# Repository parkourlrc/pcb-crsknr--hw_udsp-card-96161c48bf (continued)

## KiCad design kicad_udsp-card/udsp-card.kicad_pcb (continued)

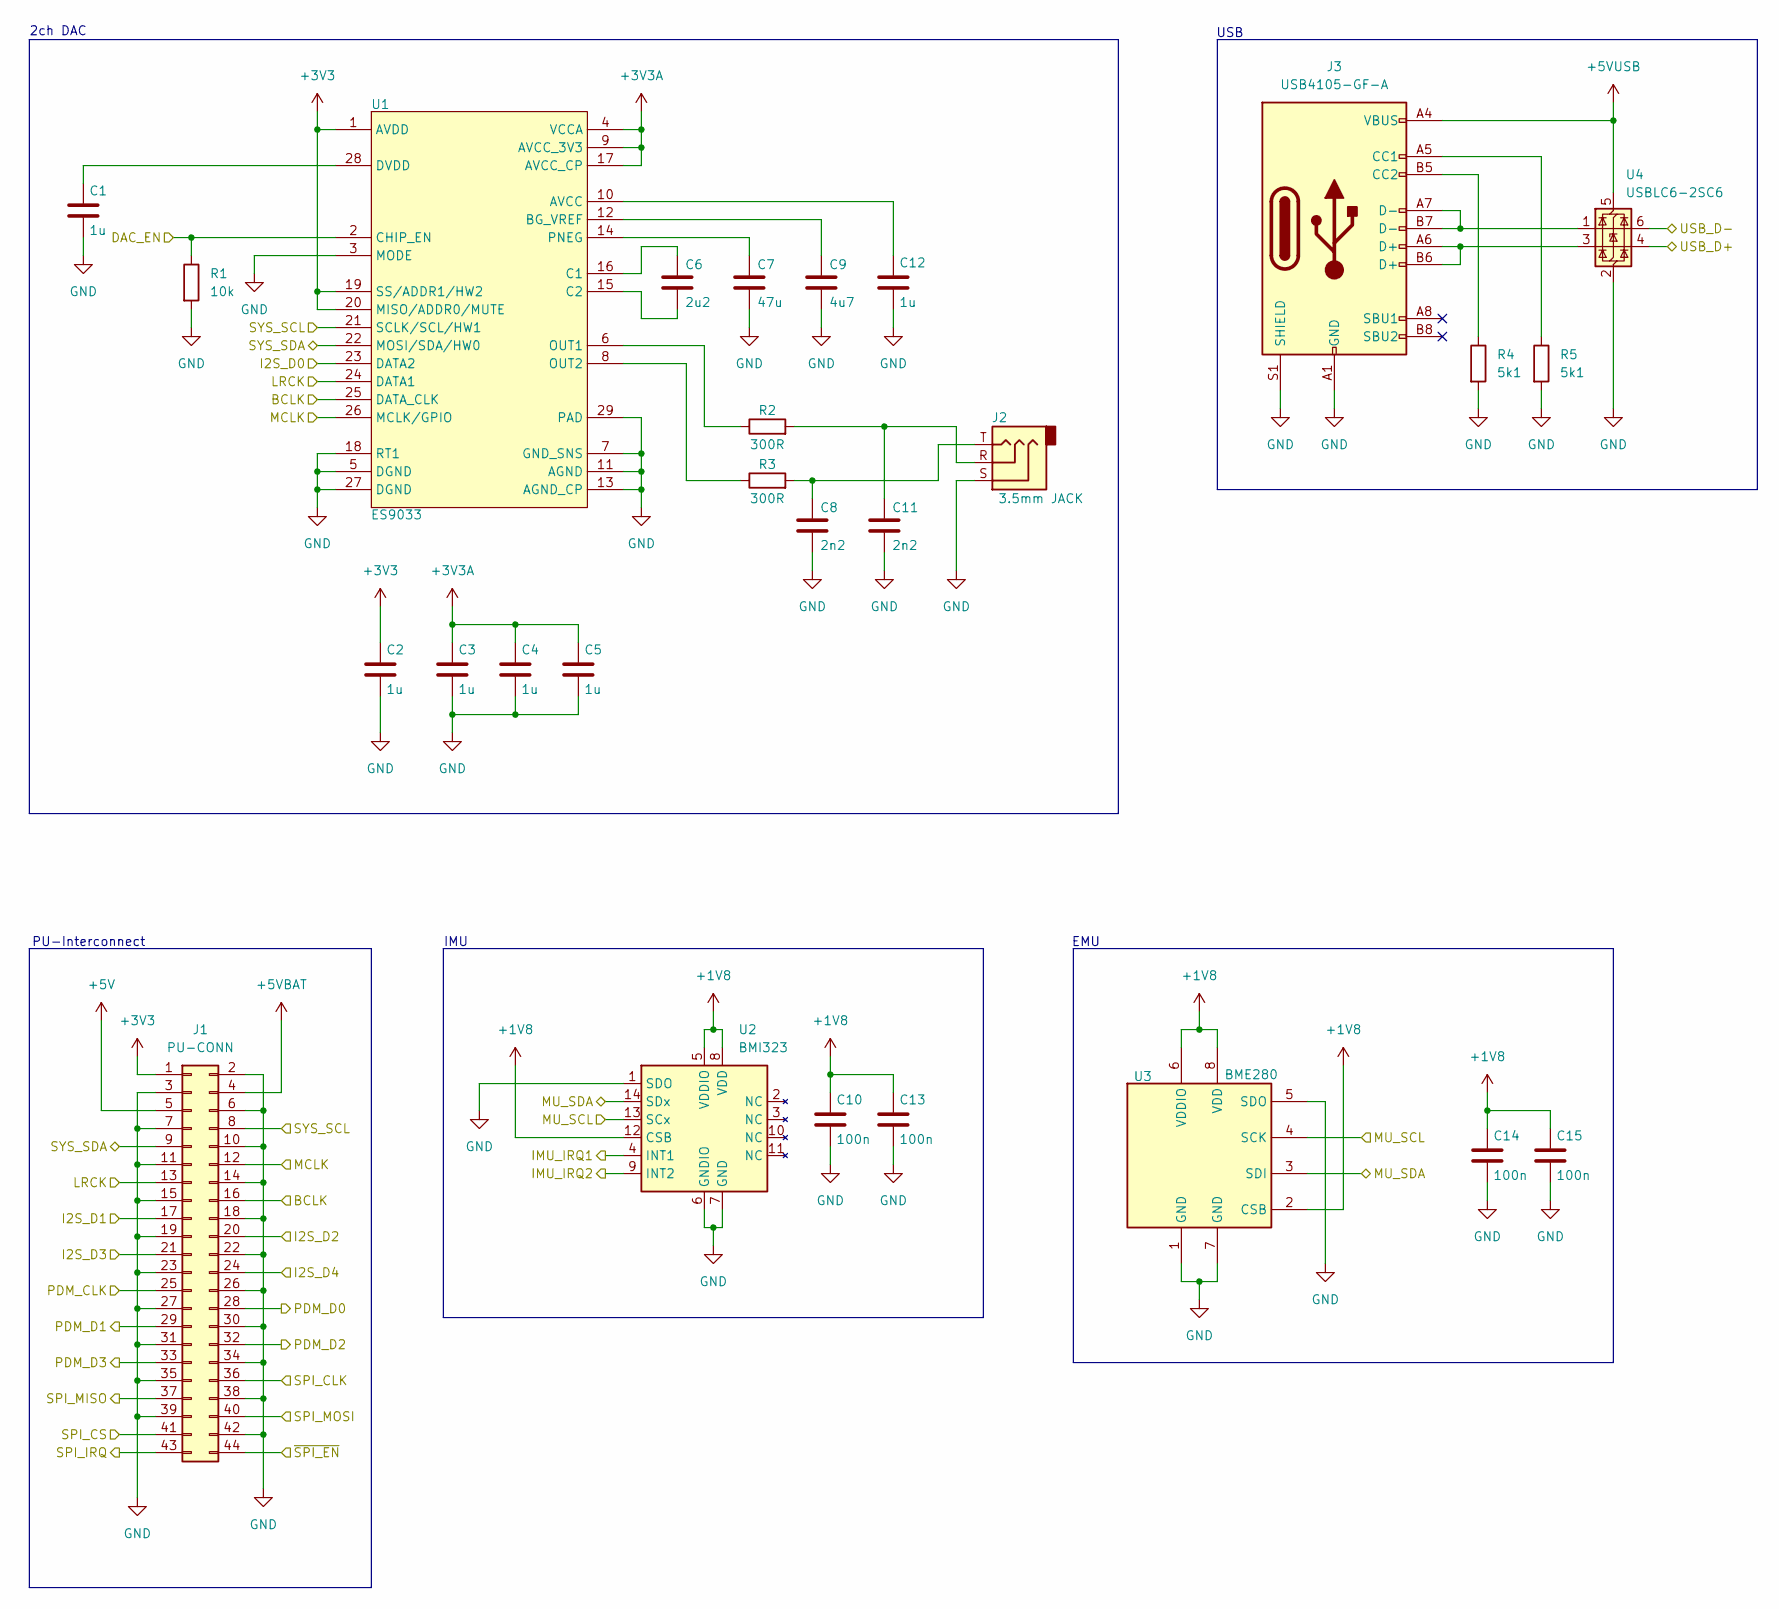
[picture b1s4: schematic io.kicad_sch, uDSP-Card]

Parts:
C1, C2, C3, C4, C5, C12: 1u; C_0402_1005Metric; Part Number CC0402KRX5R7BB105
C6: 2u2; C_0603_1608Metric; Part Number CC0603KRX5R9BB225
C7: 47u; C_0805_2012Metric; Part Number CC0805MKX5R6BB476
C8, C11: 2n2; C_0402_1005Metric; Part Number GRM1555C1H222GA01D
C9: 4u7; C_0603_1608Metric; Part Number CC0603KRX5R7BB475
C10, C13, C14, C15: 100n; C_0402_1005Metric; Part Number CC0402KRX5R9BB104
J1: PU-CONN; SAMTEC_FLE-122-01-G-DV; Part Number FLE-122-01-G-DV
J2: 3.5mm JACK; Jack_3.5mm_CUI_SJ-3523-SMT_Horizontal; Part Number SJ-3523-SMT-TR
J3: USB4105-GF-A; USB_C_Receptacle_GCT_USB4105-xx-A_16P_TopMnt_Horizontal; Part Number USB4105-GF-A
R1: 10k; R_0402_1005Metric; Part Number RC0402FR-0710KL
R2, R3: 300R; R_0402_1005Metric; Part Number RT0402FRE07300RL
R4, R5: 5k1; R_0402_1005Metric; Part Number RC0402FR-075K1L
U1: ES9033; QFN-28-1EP_5x5mm_P0.5mm_EP3.1x3.1mm; Part Number ES9033Q
U2: BMI323; Bosch_LGA-14_3x2.5mm_P0.5mm; Part Number BMI323
U3: BME280; Bosch_LGA-8_2.5x2.5mm_P0.65mm_ClockwisePinNumbering; Part Number BME280
U4: USBLC6-2SC6; SOT-23-6; Part Number USBLC6-2SC6

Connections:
+1V8: C10.1, C13.1, C14.1, C15.1, U2.5 (VDDIO), U2.8 (VDD), U2.12 (CSB), U3.2 (CSB), U3.6 (VDDIO), U3.8 (VDD); also elsewhere on the board
+3V3: C2.1, J1.1, U1.1 (AVDD), U1.19 (SS/ADDR1/HW2), U1.20 (MISO/ADDR0/MUTE); also elsewhere on the board
+3V3A: C3.1, C4.1, C5.1, U1.4 (VCCA), U1.9 (AVCC_3V3), U1.17 (AVCC_CP); also elsewhere on the board
+5V: J1.5; also elsewhere on the board
+5VBAT: J1.4; also elsewhere on the board
+5VUSB: J3.A4 (VBUS), J3.A9 (VBUS), J3.B4 (VBUS), J3.B9 (VBUS), U4.5 (VBUS); also elsewhere on the board
/DAC_EN: R1.1, U1.2 (CHIP_EN); also elsewhere on the board
/I2S.BCLK: J1.16, U1.25 (DATA_CLK); also elsewhere on the board
/I2S.D0: U1.23 (DATA2); also elsewhere on the board
/I2S.D1: J1.17; also elsewhere on the board
/I2S.D2: J1.20; also elsewhere on the board
/I2S.D3: J1.21; also elsewhere on the board
/I2S.D4: J1.24; also elsewhere on the board
/I2S.LRCK: J1.13, U1.24 (DATA1); also elsewhere on the board
/I2S.MCLK: J1.12, U1.26 (MCLK/GPIO); also elsewhere on the board
/IMU_IRQ1: U2.4 (INT1); also elsewhere on the board
/IMU_IRQ2: U2.9 (INT2); also elsewhere on the board
/MIC.CLK: J1.25; also elsewhere on the board
/MIC.D0: J1.28; also elsewhere on the board
/MIC.D1: J1.29; also elsewhere on the board
/MIC.D2: J1.32; also elsewhere on the board
/MIC.D3: J1.33; also elsewhere on the board
/MU.SCL: U2.13 (SCx), U3.4 (SCK); also elsewhere on the board
/MU.SDA: U2.14 (SDx), U3.3 (SDI); also elsewhere on the board
/SPI.CLK: J1.36; also elsewhere on the board
/SPI.CS: J1.41; also elsewhere on the board
/SPI.MISO: J1.37; also elsewhere on the board
/SPI.MOSI: J1.40; also elsewhere on the board
/SPI_IRQ: J1.43; also elsewhere on the board
/SYS.SCL: J1.8, U1.21 (SCLK/SCL/HW1); also elsewhere on the board
/SYS.SDA: J1.9, U1.22 (MOSI/SDA/HW0); also elsewhere on the board
/USB.D+: U4.4 (I/O2); also elsewhere on the board
/USB.D-: U4.6 (I/O1); also elsewhere on the board
/~SPI_EN: J1.44; also elsewhere on the board
GND: C1.2, C2.2, C3.2, C4.2, C5.2, C7.2, C8.2, C9.2, C10.2, C11.2, C12.2, C13.2, C14.2, C15.2, J1.2, J1.3, J1.6, J1.7, J1.10, J1.11, J1.14, J1.15, J1.18, J1.19, J1.22, J1.23, J1.26, J1.27, J1.30, J1.31, J1.34, J1.35, J1.38, J1.39, J1.42, J2.S, J3.A1 (GND), J3.A12 (GND), J3.B1 (GND), J3.B12 (GND), J3.S1 (SHIELD), R1.2, R4.2, R5.2, U1.3 (MODE), U1.5 (DGND), U1.7 (GND_SNS), U1.11 (AGND), U1.13 (AGND_CP), U1.18 (RT1), U1.27 (DGND), U1.29 (PAD), U2.1 (SDO), U2.6 (GNDIO), U2.7 (GND), U3.1 (GND), U3.5 (SDO), U3.7 (GND), U4.2 (GND); also elsewhere on the board
unnamed: C8.1, J2.T, R3.2
unnamed: C11.1, J2.R, R2.2
unnamed: J3.A5 (CC1), R5.1
unnamed: J3.B5 (CC2), R4.1
unnamed: J3.A6 (D+), J3.B6 (D+), U4.3 (I/O2)
unnamed: J3.A7 (D-), J3.B7 (D-), U4.1 (I/O1)
unnamed: C12.1, U1.10 (AVCC)
unnamed: C9.1, U1.12 (BG_VREF)
unnamed: C6.1, U1.16 (C1)
unnamed: C6.2, U1.15 (C2)
unnamed: C1.1, U1.28 (DVDD)
unnamed: R2.1, U1.6 (OUT1)
unnamed: R3.1, U1.8 (OUT2)
unnamed: C7.1, U1.14 (PNEG)

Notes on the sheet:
2ch DAC
IMU
USB
EMU
PU-Interconnect

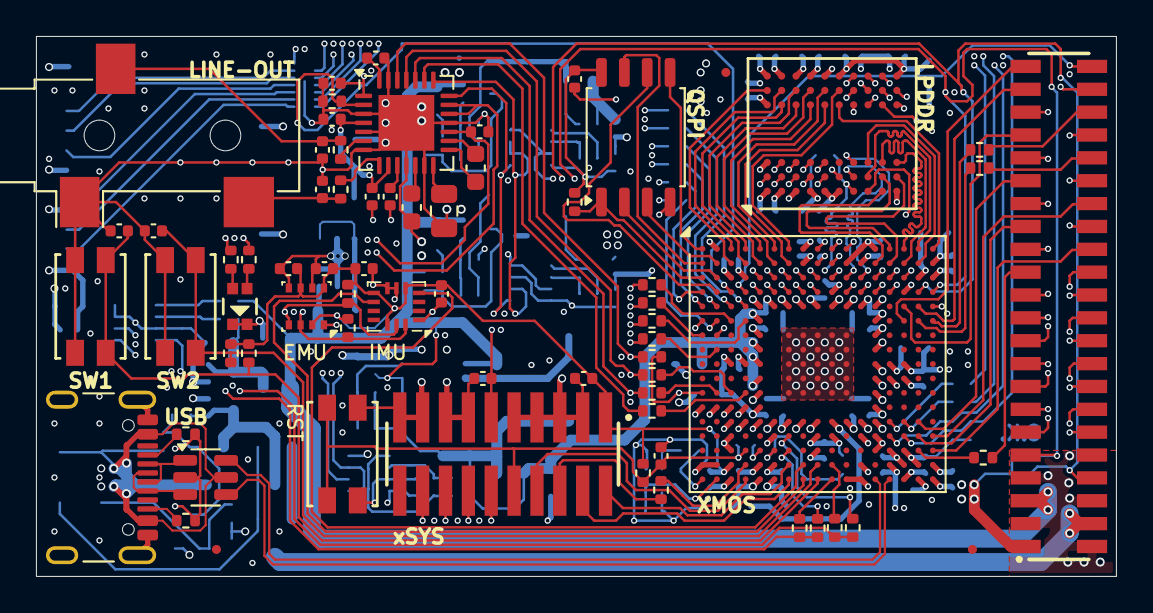
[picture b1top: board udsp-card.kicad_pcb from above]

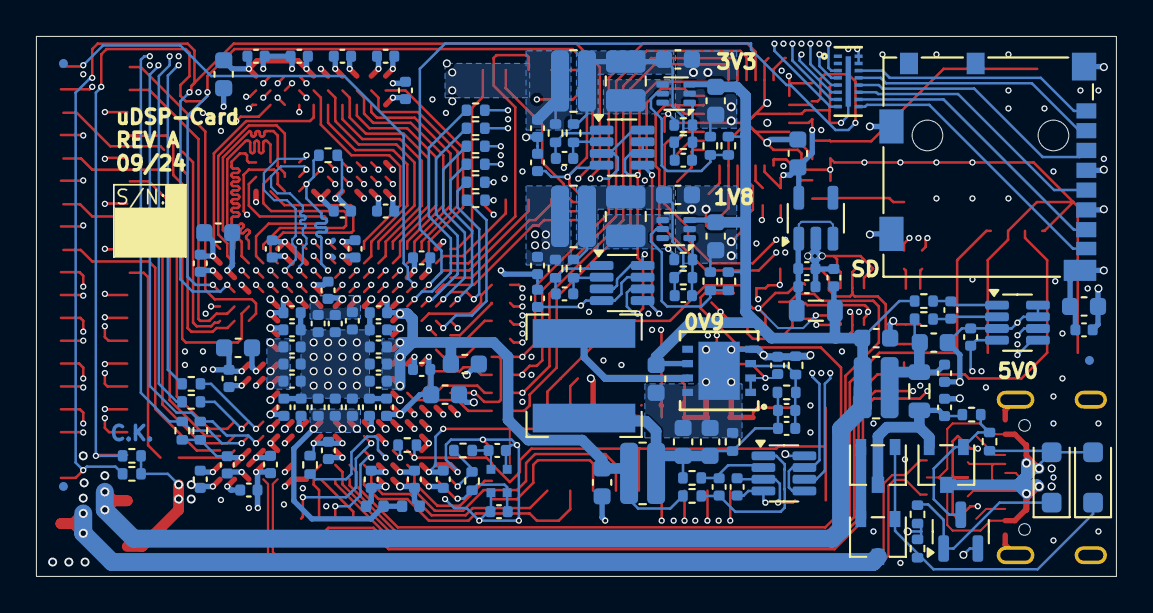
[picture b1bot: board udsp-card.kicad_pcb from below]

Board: 6 copper layers, 60.0 x 30.0 mm, 221 parts (153 on the bottom side), 183 nets.

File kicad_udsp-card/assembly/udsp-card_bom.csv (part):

"Reference","Value","Part Number","Manufacturer","Description","Footprint","Qty","Distributor Link"
"C1,C2,C3,C4,C5,C12,C16,C17,C20,C81,C83,C92,C93","1u","CC0402KRX5R7BB105","Yageo","Multilayer Ceramic Capacitor, 1uF, 16V, 10%, X5R, 0402","Capacitor_SMD:C_0402_1005Metric","13","https://www.lcsc.com/product-detail/Multilayer-Ceramic-Capac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"
"C6","2u2","CC0603KRX5R9BB225 ","Yageo","Multilayer Ceramic Capacitor, 2.2uF, 50V, 10%, X5R, 0603","Capacitor_SMD:C_0603_1608Metric","1","https://www.lcsc.com/product-detail/Multilayer-Ceramic-Capac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"
"C7","47u","CC0805MKX5R6BB476","Yageo","Multilayer Ceramic Capacitor, 47uF, 10V, 20%, X5R, 0805","Capacitor_SMD:C_0805_2012Metric","1","https://www.lcsc.com/product-detail/Multilayer-Ceramic-Capac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"
"C8,C11","2n2","GRM1555C1H222GA01D","Murata Electronics","Multilayer Ceramic Capacitor, 2.2nF, 50V, 2%, NP0, 0402","Capacitor_SMD:C_0402_1005Metric","2","https://www.lcsc.com/product-detail/Multilayer-Ceramic-Capac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"
"C9,C18,C32,C49,C56,C62","4u7","CC0603KRX5R7BB475","Yageo","Multilayer Ceramic Capacitor, 4.7uF, 16V, 10%, X5R, 0603","Capacitor_SMD:C_0603_1608Metric","6","https://www.lcsc.com/product-detail/Multilayer-Ceramic-Capac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"
"C10,C13,C14,C15,C19,C21,C22,C23,C24,C25,C26,C27,C28,C29,C30,C31,C33,C34,C35,C36,C37,C38,C39,C40,C43,C44,C45,C46,C47,C48,C50,C51,C52,C53,C54,C55,C57,C58,C59,C60,C61,C63,C64,C65,C66,C67,C68,C69,C70,C72,C73,C74,C77,C82,C96,C97,C98,C99,C100,C101,C102,C103","100n","CC0402KRX5R9BB104","Yageo","Multilayer Ceramic Capacitor, 100nF, 50V, 10%, X5R, 0402","Capacitor_SMD:C_0402_1005Metric","62","https://www.lcsc.com/product-detail/Multilayer-Ceramic-Capac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"
"C41,C42,C86,C88","18p","CC0402JRNPO9BN180","Yageo","Multilayer Ceramic Capacitor, 18pF, 50V, 5%, NP0, 0402","Capacitor_SMD:C_0402_1005Metric","4","https://www.lcsc.com/product-detail/Multilayer-Ceramic-Capac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"
"C71,C75,C76,C78,C79,C80,C87,C89,C90,C91,C94,C95","10u","CC0603MRX5R7BB106","Yageo","Multilayer Ceramic Capacitor, 10uF, 16V, 20%, X5R, 0603","Capacitor_SMD:C_0603_1608Metric","12","https://www.lcsc.com/product-detail/Multilayer-Ceramic-Capac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"
"C84","470p","CC0402KRX7R7BB471 ","Yageo","Multilayer Ceramic Capacitor, 470pF, 16V, 10%, X7R, 0402","Capacitor_SMD:C_0402_1005Metric","1","https://www.lcsc.com/product-detail/Multilayer-Ceramic-Capac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"
"C85","220p","CC0402KRX7R7BB221","Yageo","Multilayer Ceramic Capacitor, 220pF, 16V, 10%, X7R, 0402","Capacitor_SMD:C_0402_1005Metric","1","https://www.lcsc.com/product-detail/Multilayer-Ceramic-Capac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"
"D1","LTST-C195KGJRKT","LTST-C195KGJRKT","Lite-On","LED dual red/green, 2V, 20mA, 0606","lib_fp_ssh:LTST-C195KGJRKT-NPC_LTO","1","https://www.lcsc.com/product-detail/LED-Indication-Discrete_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"
"D2,D3","1N4148W","1N4148W-E3-08","Vishay Intertech","Diode, 75V, 0.15A, SOD-123F","Diode_SMD:D_SOD-123F","2","https://www.lcsc.com/product-detail/Switching-Diodes_Vishay-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"
"FB1,FB2","600R","BLM15PX601SH1D","Murata","Ferrite Bead, 600R AT 100MHz, 0.9A, 0402","Inductor_SMD:L_0402_1005Metric","2","https://www.mouser.fi/ProductDetail/Murata-Electronics/BLM15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"
"FB3,FB4","180R","BLM21SP181SZ1D","Murata","Ferrite Bead, 180R AT 100MHz, 4.0A, 0805","Inductor_SMD:L_0805_2012Metric","2","https://www.lcsc.com/product-detail/Ferrite-Beads_Murata-Ele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"
"J1","PU-CONN","FLE-122-01-G-DV","Samtec","Socket, 0.050"" Pitch, 2x22, SMD","lib_fp_ssh:SAMTEC_FLE-122-01-G-DV","1","https://www.mouser.fi/ProductDetail/Samtec/FLE-122-01-G-DV-P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"
"J2","3.5mm JACK","SJ-3523-SMT-TR ","CUI Devices","Audio Jack, 3 Poles (Stereo / TRS), SMD","Connector_Audio:Jack_3.5mm_CUI_SJ-3523-SMT_Horizontal","1","https://www.mouser.fi/ProductDetail/CUI-Devices/SJ-3523-SMT-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"
"J3","USB4105-GF-A","USB4105-GF-A","GCT","USB 2.0-only 16P Type-C Receptacle connector","Connector_USB:USB_C_Receptacle_GCT_USB4105-xx-A_16P_TopMnt_Horizontal","1","https://www.mouser.fi/ProductDetail/GCT/USB4105-GF-A?qs=KUoI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"
"J4","xSYS2","FTSH-110-01-F-DV-K","Samtec","Header, 0.050"" Pitch, 2x10, SMD","lib_fp_ssh:SAMTEC_FTSH-110-01-F-DV-TR","1","https://www.lcsc.com/product-detail/Pin-Headers_Samtec-FTSH-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"
"J5","104031-0811","104031-0811","Molex","Micro SD Card Socket with two card detection pins","Connector_Card:microSD_HC_Molex_104031-0811","1","https://www.lcsc.com/product-detail/SD-Card-Memory-Card-Conn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"
"L1,L2","1u5","MAMK2520H1R5M","Taiyo Yuden","Power Inductor, 1.5uH, 2.6A, 65mR DCR, 2.5x2.0x1.2mm, SMD","Inductor_SMD:L_1008_2520Metric","2","https://www.lcsc.com/product-detail/Power-Inductors_Taiyo-Yu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"
"L3","2u2","NR6028T2R2N","Taiyo Yuden","Power Inductor, 2.2uH, 3.7A, 26mR DCR, SMD","Inductor_SMD:L_Bourns-SRN6028","1","https://www.mouser.fi/ProductDetail/TAIYO-YUDEN/NR6028T2R2N?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"
"Q1","2N7002","2N7002A-7","Diodes Incorporated","N-Channel MOSFET, 0.115A, 60V, SOT-23","Package_TO_SOT_SMD:SOT-23","1","https://www.lcsc.com/product-detail/MOSFETs_Diodes-Incorpora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"
"Q2,Q3,Q4","RQ5C060BCTCL","RQ5C060BCTCL","ROHM Semiconductor ","P-Channel MOSFET, 6A, 20V, SOT-346","lib_fp_ssh:SOT346","3","https://www.lcsc.com/product-detail/MOSFETs_ROHM-Semicon-RQ5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"
"R1,R33,R34,R39,R45,R46,R48,R49,R50,R56,R59","10k","RC0402FR-0710KL","Yageo","Thick Film Resistor, 10kOhm, 62.5mW, 1%, 100ppm, 0402","Resistor_SMD:R_0402_1005Metric","11","https://www.lcsc.com/product-detail/Chip-Resistor-Surface-Mo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"
"R2,R3","300R","RT0402FRE07300RL","Yageo","Thin Film Resistor, 300Ohm, 62.5mW, 1%, 50ppm, 0402","Resistor_SMD:R_0402_1005Metric","2","https://www.mouser.fi/ProductDetail/YAGEO/RT0402FRE07300RL?q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"
"R4,R5,R20,R21,R35,R36","5k1","RC0402FR-075K1L","Yageo","Thick Film Resistor, 5.1kOhm, 62.5mW, 1%, 100ppm, 0402","Resistor_SMD:R_0402_1005Metric","6","https://www.lcsc.com/product-detail/Chip-Resistor-Surface-Mo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"
"R6,R7,R8,R9,R10,R11,R12,R13,R14,R15,R16,R17,R18,R19,R27,R40,R41,R42,R43,R44","33R","RC0402FR-0733RL","Yageo","Thick Film Resistor, 33Ohm, 62.5mW, 1%, 100ppm, 0402","Resistor_SMD:R_0402_1005Metric","20","https://www.lcsc.com/product-detail/Chip-Resistor-Surface-Mo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"
"R22","1M","RC0402FR-071ML","Yageo","Thick Film Resistor, 1MOhm, 62.5mW, 1%, 100ppm, 0402","Resistor_SMD:R_0402_1005Metric","1","https://www.lcsc.com/product-detail/Chip-Resistor-Surface-Mo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"
"R30,R31,R32","680R","RC0402FR-07680RL","Yageo","Thick Film Resistor, 680Ohm, 62.5mW, 1%, 100ppm, 0402","Resistor_SMD:R_0402_1005Metric","3","https://www.lcsc.com/product-detail/Chip-Resistor-Surface-Mo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"
"R51","0R01","ERJ-D2DFR010V","Panasonic","Thick Film Resistor, 10mOhm, 1W, 1%, 100ppm, 0612","Resistor_SMD:R_0612_1632Metric","1","https://www.mouser.fi/ProductDetail/Panasonic/ERJ-D2DFR010V?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"
"R57,R64","2k2","RC0402FR-072K2L","Yageo","Thick Film Resistor, 2.2kOhm, 62.5mW, 1%, 100ppm, 0402","Resistor_SMD:R_0402_1005Metric","2","https://www.lcsc.com/product-detail/Chip-Resistor-Surface-Mo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"
"R58,R60","20k","RC0402FR-0720KL","Yageo","Thick Film Resistor, 20kOhm, 62.5mW, 1%, 100ppm, 0402","Resistor_SMD:R_0402_1005Metric","2","https://www.lcsc.com/product-detail/Chip-Resistor-Surface-Mo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"
"R61","160k","RC0402FR-07160KL","Yageo","Thick Film Resistor, 160kOhm, 62.5mW, 1%, 100ppm, 0402","Resistor_SMD:R_0402_1005Metric","1","https://www.lcsc.com/product-detail/Chip-Resistor-Surface-Mo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"
"R62,R63,R65","0R047","ERJ-D2CFR047V","Panasonic","Thick Film Resistor, 47mOhm, 1W, 1%, 100ppm, 0612","Resistor_SMD:R_0612_1632Metric","3","https://www.mouser.fi/ProductDetail/Panasonic/ERJ-D2CFR047V?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"
"R66,R67,R68,R69,R70,R71,R72,R73","10R","RC0402FR-0710RL","Yageo","Thick Film Resistor, 10Ohm, 62.5mW, 1%, 100ppm, 0402","Resistor_SMD:R_0402_1005Metric","8","https://www.lcsc.com/product-detail/Chip-Resistor-Surface-Mo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"
"SW1,SW2,SW3","EVQ-P2F02K","EVQ-P2F02K","Panasonic","Tactile Switch, Light Touch Switch, 4.7x3.5mm SMD","lib_fp_ssh:EVQP2K_PAN","3","https://www.mouser.fi/ProductDetail/Panasonic/EVQ-P2F02K?qs=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"
"U1","ES9033","ES9033Q","ESS Technology","D/A Converter, 2 Channel, QFN-28","Package_DFN_QFN:QFN-28-1EP_5x5mm_P0.5mm_EP3.1x3.1mm","1","https://www.mouser.fi/ProductDetail/ESS-Technology/ES9033Q?q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"
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
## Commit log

2025-07-10 typo
2025-07-10 change reference
